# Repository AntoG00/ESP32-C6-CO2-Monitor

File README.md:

# ESP32-C6 E-Paper Air Quality Monitor

A high-precision, open-hardware environmental monitor designed to track CO2, Temperature, and Humidity levels. The device is built around the RISC-V based ESP32-C6 and features a raw E-Paper panel with a custom-designed boost driver to ensure zero light pollution and minimal thermal self-heating.

## Key Features
*   **MCU:** Espressif **ESP32-C6-Mini-1** (RISC-V, Wi-Fi 6, BLE 5, Zigbee).
*   **Sensors:**
    *   **SCD43 (Sensirion):** Photoacoustic NDIR CO2 sensor for high-accuracy indoor air quality monitoring.
    *   **SHT45-AD1F (Sensirion):** Ultra-high precision (±1.0% RH, ±0.1°C) temperature and humidity sensor with integrated PTFE membrane for protection.
*   **Display:** **Pervasive Displays E2266QS0F1** (2.66" E-Paper/E-Ink).
*   **Power:** USB-C powered via a high-efficiency, low-noise LDO (**TLV75733**). Designed for continuous operation without batteries.

## Engineering Design Decisions
This project involved several specific hardware design challenges:

1.  **Thermal Isolation (Mechanical/Electrical):** To prevent the heat generated by the MCU and voltage regulators from biasing the sensitive SHT45 and SCD43 readings, the sensors are physically isolated on the PCB using milling slots (thermal cutouts) and thin connecting bridges.
2.  **Custom E-Paper Driver:** Instead of using a pre-made display module, I integrated the high-voltage boost converter (generating ~15V) directly onto the main PCB using a specialized power inductor ($I_{sat} > 800mA$), N-Channel MOSFET, and Schottky diode topology.
3.  **Signal Integrity:** The schematic includes specific filtering for the photoacoustic sensor's peak current demands and a dedicated boot-strapping circuit to ensure reliable flashing via the native USB interface.

## PCB Layout & Thermal Engineering
The design utilizes a **4-layer stack-up** to ensure solid Ground return paths and stable power delivery for the ESP32's RF radio.

A dedicated **thermal isolation slot** separates the board into two distinct thermal zones:
*   **Right Side (Hot Zone):** Contains the ESP32 MCU, Power Regulation, and Boost Converter.
*   **Left Side (Cold Zone):** Contains the environmental sensors, connected only by narrow FR4 bridges to minimize thermal conductivity.

## Status
*   [x] Schematic Design & Verification
*   [x] PCB Layout (4-Layer)
*   [ ] Manufacturing & Assembly

## License
MIT License

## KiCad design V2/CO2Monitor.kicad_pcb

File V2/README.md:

# Hardware V2 – ESP32‑C6 + SEN66 + 4.2" E‑Ink

This is the second hardware revision of the project. V2 replaces the SCD43 + SHT45 combo with a single Sensirion **SEN66** environmental sensor and upgrades the display.

## Main Components

- **MCU:** Espressif **ESP32‑C6 Mini**
  - Wi‑Fi 6 + BLE / 802.15.4 capable (WiFi 6, Zigbee, Thread)
- **Sensor:** Sensirion **SEN66**
  - PM1, PM2.5, PM4, PM10
  - Temperature, Relative Humidity
  - VOC Index, NOx Index, CO₂
- **Display:** Pervasive Displays **4.2" Spectra E2417QS0A3**
  - 3‑color E‑Ink
- **Status LED:** Inolux **IN‑PI33TBTPRPGPB** multi‑color LED
  - Used for debug / status indication via color patterns

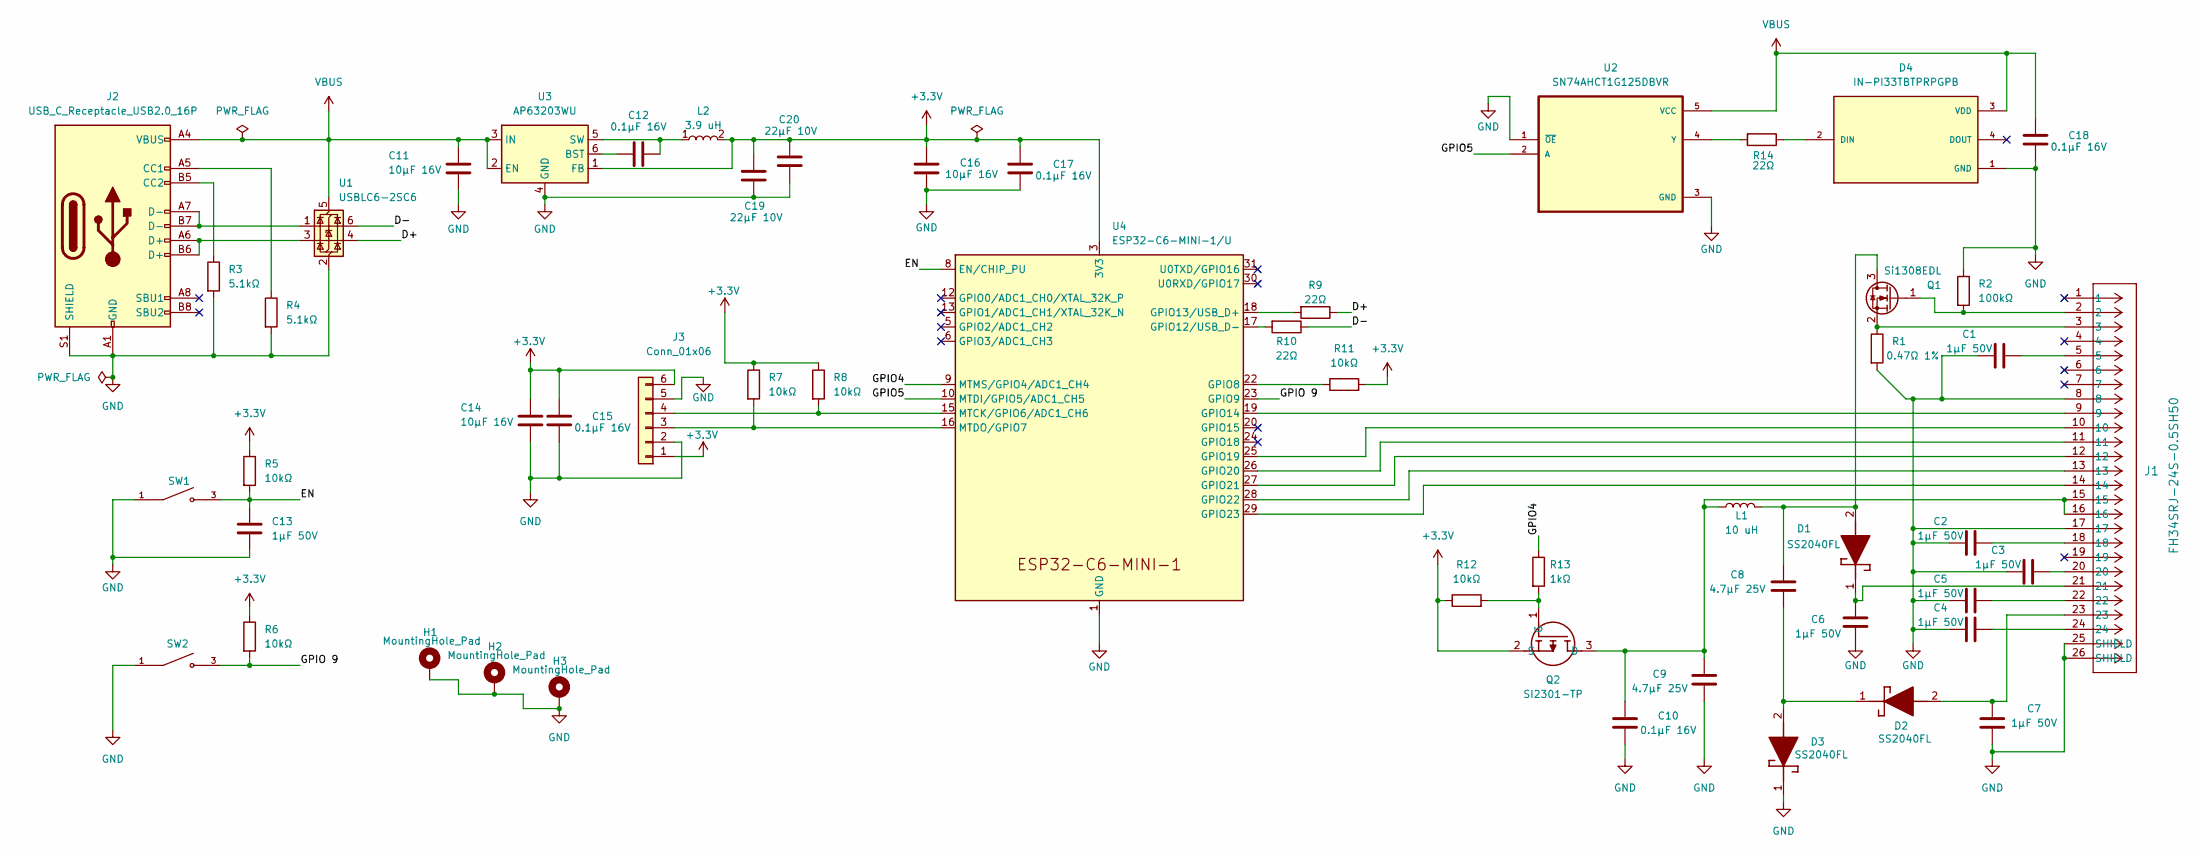
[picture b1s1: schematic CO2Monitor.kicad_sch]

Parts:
C1, C2, C3, C4, C5, C6, C7, C13: 1µF 50V; C_0603_1608Metric
C8, C9: 4.7µF 25V; C_1206_3216Metric
C10, C12, C15, C17, C18: 0.1µF 16V; C_0402_1005Metric
C11, C14, C16: 10µF 16V; C_0805_2012Metric
C19, C20: 22µF 10V; C_1206_3216Metric
D1, D2, D3: SS2040FL; SODFL3618X110N; Mouser Part Number 241-SS2040FLR100001
D4: IN-PI33TBTPRPGPB; LED_IN-PI33TBTPRPGPB; PARTREV 1.2
H1, H2, H3: MountingHole_Pad; MountingHole_3.2mm_M3_ISO14580_Pad
J1: FH34SRJ-24S-0.5SH50; CONN24x1_FH34SRJ-24S-0.5SH50_HIR
J2: USB_C_Receptacle_USB2.0_16P; GCT_USB4145-03-0230-C_REVA2
J3: Conn_01x06; JST_GH_SM06B-GHS-TB_1x06-1MP_P1.25mm_Horizontal
L1: 10 uH; L_Bourns-SRN4018
L2: 3.9 uH; INDPM5050X400N
Q1: Si1308EDL; SOT-323_SC-70
Q2: SI2301-TP; SOT95P237X125-3N; Mouser Part Number 833-SI2301-TP
R1: 0.47Ω 1%; R_1206_3216Metric
R2: 100kΩ; R_0603_1608Metric
R3, R4: 5.1kΩ; R_0603_1608Metric
R5, R6, R7, R8, R11, R12: 10kΩ; R_0603_1608Metric
R9, R10, R14: 22Ω; R_0603_1608Metric
R13: 1kΩ; R_0603_1608Metric
SW1, SW2: 2-1437565-8; SW_2-1437565-8; PARTREV V
U1: USBLC6-2SC6; SOT-23-6
U2: SN74AHCT1G125DBVR; SOT95P280X145-5N
U3: AP63203WU; TSOT-23-6
U4: ESP32-C6-MINI-1/U; ESP32-C6-MINI-1

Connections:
+3.3V: C14.1, C15.1, C16.2, C17.1, C19.1, C20.1, J3.1, J3.6, L2.2, Q2.2 (S), R5.1, R6.1, R7.1, R8.1, R11.2, R12.1, U3.1 (FB), U4.3 (3V3)
/D+: R9.1, U1.4 (I/O2)
/D-: R10.1, U1.6 (I/O1)
/EN: C13.2, R5.2, SW1.3, SW1.4, U4.8 (EN/CHIP_PU)
/GPIO4: R13.1, U4.9 (MTMS/GPIO4/ADC1_CH4)
/GPIO5: U2.2 (A), U4.10 (MTDI/GPIO5/ADC1_CH5)
/GPIO 9: R6.2, SW2.3, SW2.4, U4.23 (GPIO9)
GND: C1.1, C2.1, C3.1, C4.1, C5.1, C6.1, C7.1, C9.2, C10.2, C11.2, C13.1, C14.2, C15.2, C16.1, C17.2, C18.2, C19.2, C20.2, D3.1 (K), D4.1 (GND), H1.1, H2.1, H3.1, J1.8, J1.17, J1.25 (SHIELD), J1.26 (SHIELD), J2.A1 (GND), J2.A12 (GND), J2.B1 (GND), J2.B12 (GND), J2.S1 (SHIELD), J3.2, J3.5, R1.2, R2.1, R3.2, R4.2, SW1.1, SW1.2, SW2.1, SW2.2, U1.2 (GND), U2.1 (~OE), U2.3 (GND), U3.4 (GND), U4.1 (GND), U4.2 (GND), U4.11 (GND), U4.14 (GND), U4.36 (GND), U4.37 (GND), U4.38 (GND), U4.39 (GND), U4.40 (GND), U4.41 (GND), U4.42 (GND), U4.43 (GND), U4.44 (GND), U4.45 (GND), U4.46 (GND), U4.47 (GND), U4.48 (GND), U4.49 (GND), U4.50 (GND), U4.51 (GND), U4.52 (GND), U4.53 (GND)
unnamed: C1.2, J1.5
unnamed: C2.2, J1.18
unnamed: C3.2, J1.20
unnamed: C4.2, J1.24
unnamed: C5.2, J1.22
unnamed: C8.2, D1.2 (A), L1.2, Q1.3 (D)
unnamed: C6.2, D1.1 (K), J1.21
unnamed: C7.2, D2.2 (A), J1.23
unnamed: C8.1, D2.1 (K), D3.2 (A)
unnamed: D4.2 (DIN), R14.1
unnamed: J2.A5 (CC1), R4.1
unnamed: J2.B5 (CC2), R3.1
unnamed: J2.A6 (D+), J2.B6 (D+), U1.3 (I/O2)
unnamed: J2.A7 (D-), J2.B7 (D-), U1.1 (I/O1)
unnamed: J3.3, R7.2, U4.16 (MTDO/GPIO7)
unnamed: J3.4, R8.2, U4.15 (MTCK/GPIO6/ADC1_CH6)
unnamed: J1.2, Q1.1 (G), R2.2
unnamed: J1.3, Q1.2 (S), R1.1
unnamed: C9.1, C10.1, J1.15, J1.16, L1.1, Q2.3 (D)
unnamed: Q2.1 (G), R12.2, R13.2
unnamed: R14.2, U2.4 (Y)
unnamed: C12.1, U3.6 (BST)
unnamed: C12.2, L2.1, U3.5 (SW)
unnamed: R11.1, U4.22 (GPIO8)
unnamed: R10.2, U4.17 (GPIO12/USB_D-)
unnamed: R9.2, U4.18 (GPIO13/USB_D+)
unnamed: J1.9, U4.19 (GPIO14)
unnamed: J1.10, U4.25 (GPIO19)
unnamed: J1.11, U4.26 (GPIO20)
unnamed: J1.12, U4.27 (GPIO21)
unnamed: J1.13, U4.28 (GPIO22)
unnamed: J1.14, U4.29 (GPIO23)
VBUS: C11.1, C18.1, D4.3 (VDD), J2.A4 (VBUS), J2.A9 (VBUS), J2.B4 (VBUS), J2.B9 (VBUS), U1.5 (VBUS), U2.5 (VCC), U3.2 (EN), U3.3 (IN)

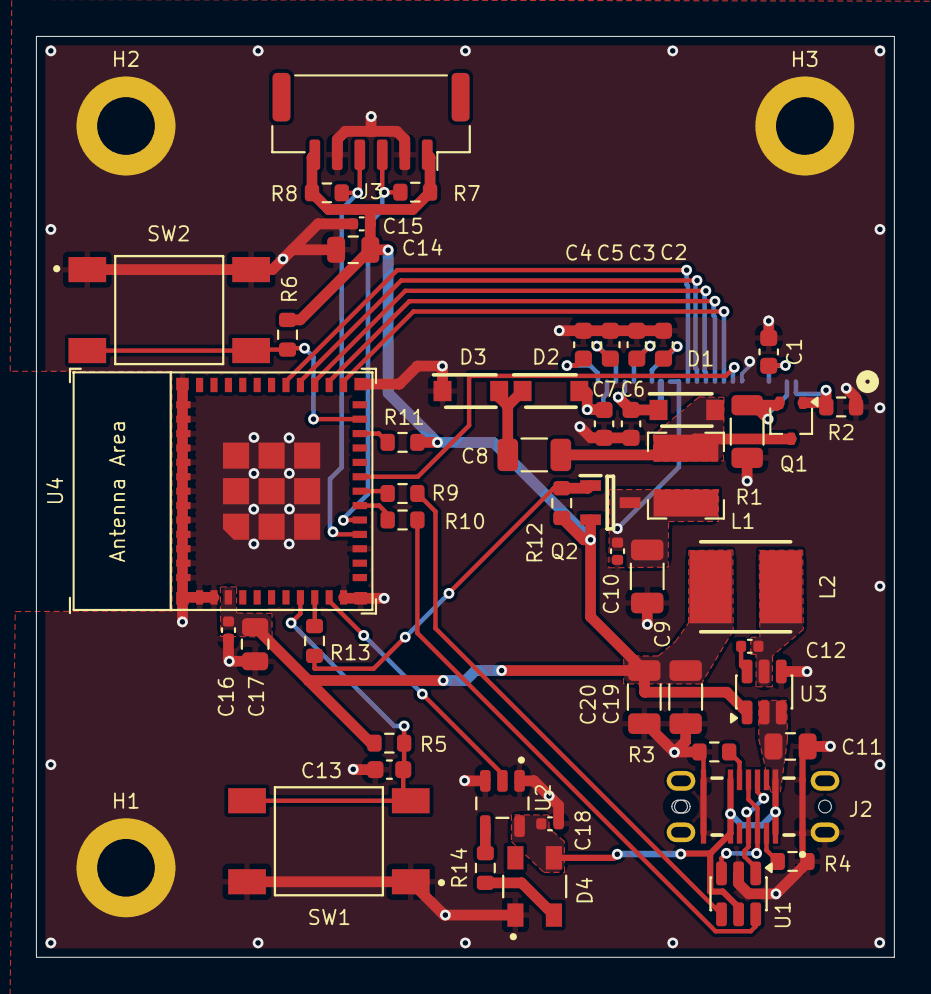
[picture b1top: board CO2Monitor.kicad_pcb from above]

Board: 2 copper layers, 47.7 x 51.2 mm, 54 parts (1 on the bottom side), 41 nets.

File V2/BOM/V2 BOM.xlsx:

|  |  | BOM
Item # | *Designator | *Qty | Manufacturer | *Mfg Part # | Description / Value | *Package/Footprint | Your Instructions / Notes
1.0 | C1,C2,C3,C4,C5,C6,C7,C13 | 8.0 |  | 1µF 50V | Cap Ceramic 1µF 50V X7R 10% | Capacitor_SMD:C_0603_1608Metric
2.0 | C8,C9 | 2.0 |  | 4.7µF 25V | Cap Ceramic 4.7µF 25V X7R 10% | Capacitor_SMD:C_1206_3216Metric
3.0 | C10,C12,C15,C17,C18 | 5.0 |  | 0.1µF 16V | Cap Ceramic 0.1µF 16V (or 25V) X7R 10% | Capacitor_SMD:C_0402_1005Metric
4.0 | C11,C14,C16 | 3.0 |  | 10µF 16V | Cap Ceramic 10µF 16V (or 25V) X5R/X7R 10% | Capacitor_SMD:C_0805_2012Metric
5.0 | C19,C20 | 2.0 |  | 22µF 10V | Cap Ceramic 22µF 10V (or 16V) X5R/X7R 20% | Capacitor_SMD:C_1206_3216Metric
6.0 | D1,D2,D3 | 3.0 | Panjit | SS2040FL_R1_00001 | Schottky Diodes & Rectifiers 40V,Schottky,SOD-123FL,2A | SS2040FL:SODFL3618X110N | https://www2.mouser.com/datasheet/3/3736/1/774A80C0874A6CB80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
7.0 | D4 | 1.0 | Inolux | IN-PI33TBTPRPGPB | Multi-Colour LEDs Top View / PLCC / 3.5 x 3.5 x 1.95 / 4-pin / Tricolor with IC | IN-PI33TBTPRPGPB:LED_IN-PI33TBTPRPGPB | https://www2.mouser.com/datasheet/3/760/1/IN_PI33TBTPRPGPB_v1.2.pdf
8.0 | J1 | 1.0 | Hirose Connector | FH34SRJ-24S-0.5SH50 | FFC & FPC Connectors 24POS .5MM | FH34SRJ-24S-0.5SH(50):CONN24x1_FH34SRJ-24S-0.5SH50_HIR | https://www2.mouser.com/datasheet/3/731/1/FH34SRJ_24S_0.5SH_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
9.0 | J2 | 1.0 | GCT | USB4145-03-0230-C | USB Connectors USB-C Rec 3u" Vert 16P SMT 2.3mm TH stakes H7.46mm T+R+Cap | USB4145-03-0230-C:GCT_USB4145-03-0230-C_REVA2 | https://www.mouser.com/catalog/specsheets/Global_Connector_T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
10.0 | J3 | 1.0 | JST Commercial | SM06B-GHS-TB | Headers & Wire Housings | Connector_JST:JST_GH_SM06B-GHS-TB_1x06-1MP_P1.25mm_Horizontal | https://www2.mouser.com/datasheet/3/1070/1/eGH.pdf
11.0 | L1 | 1.0 | Bourns | SRN4018-100M | Power Inductors - SMD 10uH 20% SMD 4018 | Inductor_SMD:L_Bourns-SRN4018 | Power Inductor, Shielded, Isat > 0.5A, DCR < 0.5Ω
12.0 | L2 | 1.0 | Bourns | SRN5040-4R7M | Power Inductors - SMD 4.7uH 20% SMD 5040 | SRN5040:INDPM5050X400N | 4.7 µH SMD shielded/semi‑shielded power inductor, Irms ≥ 3.0 A, Isat ≥ 3.0 A, D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
13.0 | Q1 | 1.0 | Vishay | SI1308EDL-T1-GE3 | MOSFETs 30V Vds 12V Vgs SC70-3 | Package_TO_SOT_SMD:SOT-323_SC-70 | https://www.vishay.com/doc?63399
14.0 | Q2 | 1.0 | Micro Commercial Components (MCC) | SI2301-TP | MOSFETs P-CH -20V -2.8A 8S | SI2301-TP:SOT95P237X125-3N | https://eu.mouser.com/datasheet/3/225/1/SI2301(SOT-23).pdf
15.0 | R1 | 1.0 |  | 0.47Ω 1% | Res Current Sense 0.47Ω 1% 1/4W | Resistor_SMD:R_1206_3216Metric
16.0 | R2 | 1.0 |  | 100kΩ | Res Thick Film 100kΩ 1% 1/10W | Resistor_SMD:R_0603_1608Metric
17.0 | R3,R4 | 2.0 |  | 5.1kΩ | Res Thick Film 5.1kΩ 1% 1/10W | Resistor_SMD:R_0603_1608Metric
18.0 | R5,R6,R7,R8,R11,R12 | 6.0 |  | 10kΩ | Res Thick Film 10kΩ 1% 1/10W | Resistor_SMD:R_0603_1608Metric
19.0 | R9,R10,R14 | 3.0 |  | 22Ω | Res Thick Film 22Ω 1% 1/10W | Resistor_SMD:R_0603_1608Metric
20.0 | R13 | 1.0 |  | 1kΩ | Res Thick Film 1kΩ 1% 1/10W | Resistor_SMD:R_0603_1608Metric
21.0 | SW1,SW2 | 2.0 | TE Connectivity / P&B | 2-1437565-8 | Tactile Switches TACTILE 260G FORCE S | TE Connectivity 2-1437565-8:SW_2-1437565-8 | Or Generic 6x6mm SMD Switch
22.0 | U1 | 1.0 | STMicroelectronics | USBLC6-2SC6 | ESD Protection Diodes / TVS Diodes ESD Protection Low Cap | Package_TO_SOT_SMD:SOT-23-6 | https://www.st.com/resource/en/datasheet/usblc6-2.pdf
23.0 | U2 | 1.0 | Texas Instruments | SN74AHCT1G125DBVR | Buffers & Line Drivers Tri-State Single Bus A 595-SN74AHCT1G125 A 595-SN74AHCT1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 | SN74AHCT1G125DBVR:SOT95P280X145-5N | https://www.ti.com/lit/gpn/sn74ahct1g125
24.0 | U3 | 1.0 | Diodes Incorporated | AP63203WU | Switching Voltage Regulators DCDC Conv HV Buck TSOT26 T&R 3K | Package_TO_SOT_SMD:TSOT-23-6 | https://4donline.ihs.com/images/VipMasterIC/IC/DIOD/DIOD-S-A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
25.0 | U4 | 1.0 | Espressif Systems | ESP32-C6-MINI-1-H8 | ESP32-C6-MINI-1-H8 | PCM_Espressif:ESP32-C6-MINI-1 | https://www.mouser.com/catalog/specsheets/Espressif_Systems_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
Need a quick and accurante quote? Need an efficient production? Please read SMT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
Click for Instructions on How to Create a BOM

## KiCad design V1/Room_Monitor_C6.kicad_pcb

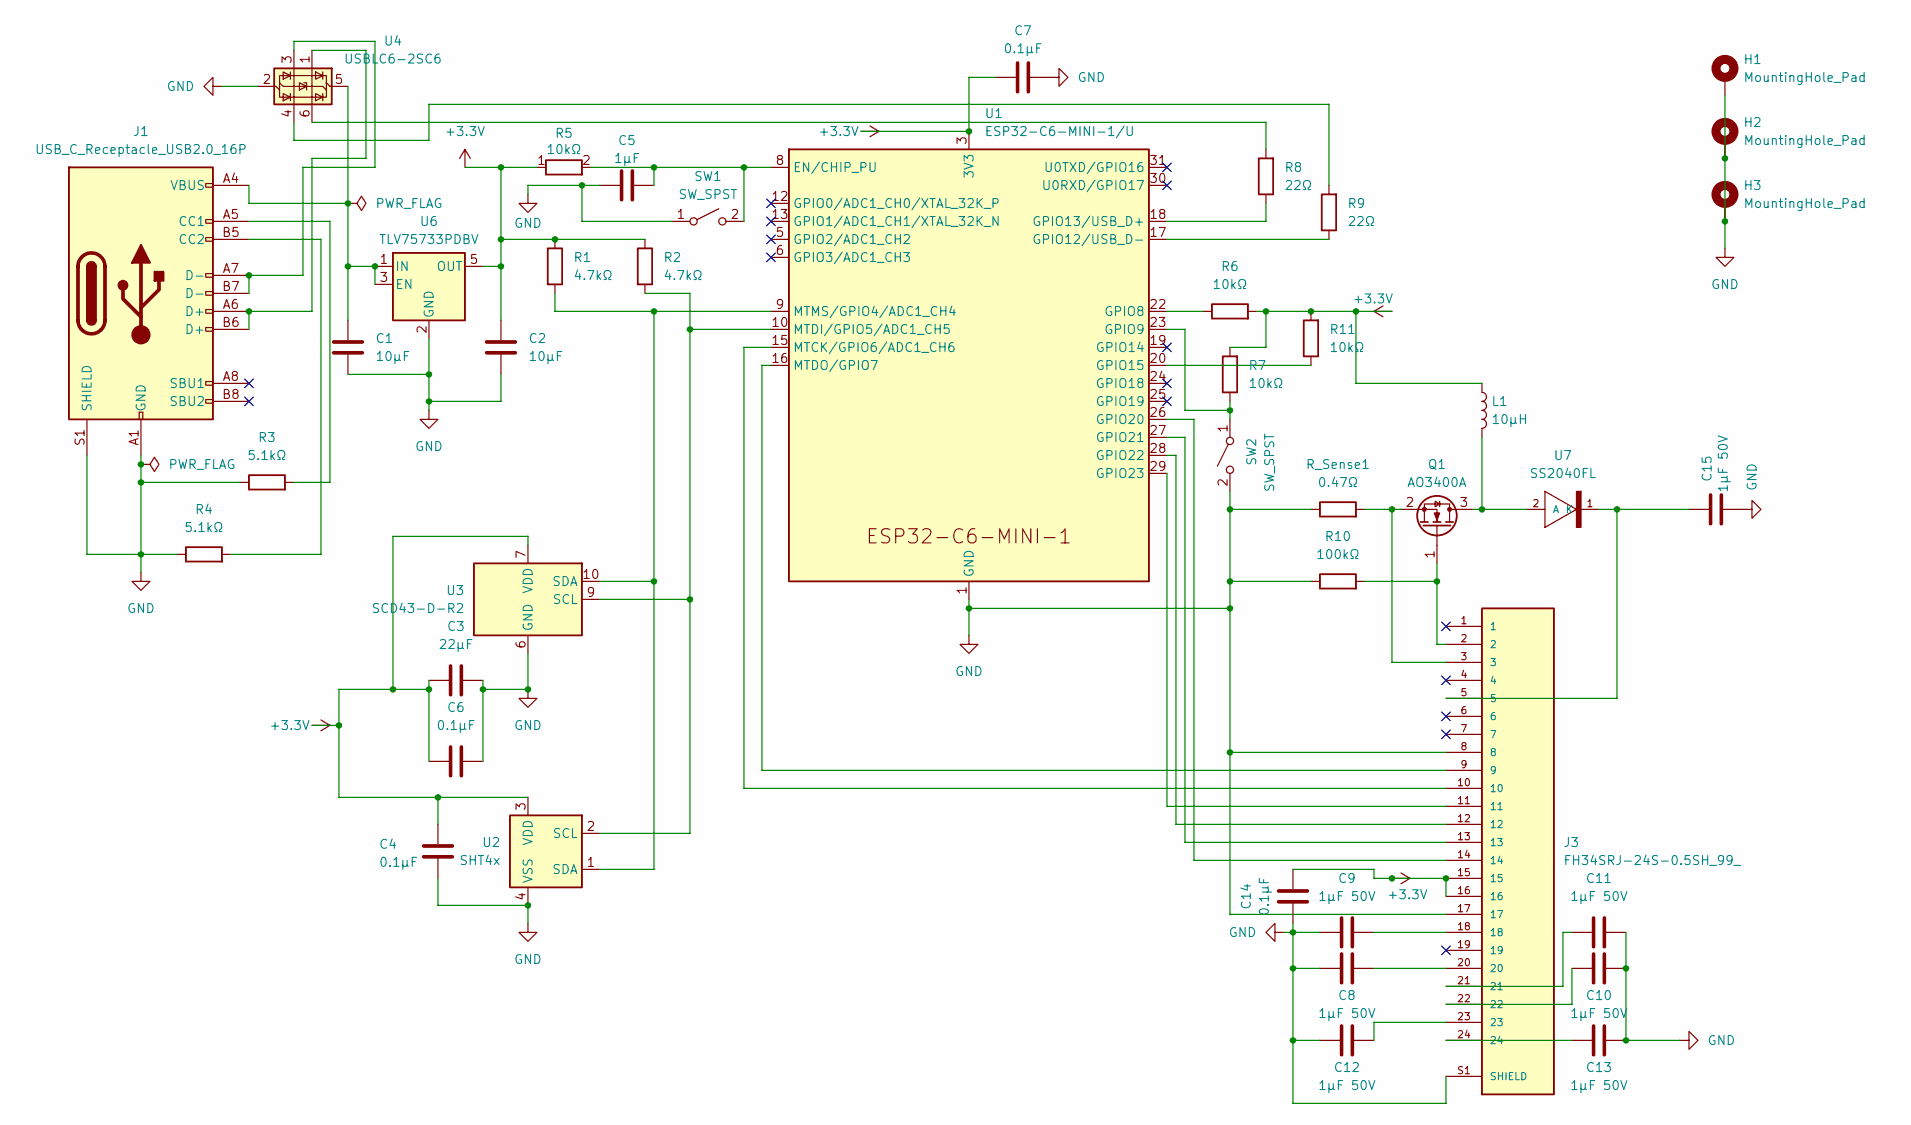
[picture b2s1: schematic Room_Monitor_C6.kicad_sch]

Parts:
C1, C2: 10µF; C_0805_2012Metric
C3: 22µF; C_0805_2012Metric
C4, C6, C7, C14: 0.1µF; C_0402_1005Metric
C5: 1µF; C_0402_1005Metric
C8, C9, C10, C11, C12, C13, C15: 1µF 50V; C_0603_1608Metric
H1, H2, H3: MountingHole_Pad; MountingHole_2.2mm_M2_Pad
J1: USB_C_Receptacle_USB2.0_16P; USB_C_Receptacle_GCT_USB4105-xx-A_16P_TopMnt_Horizontal
J3: FH34SRJ-24S-0.5SH_99_; HRS_FH34SRJ-24S-0.5SH_99_; PARTREV NA; DigiKey_Part_Number H124725CT-ND
L1: 10µH; L_Taiyo-Yuden_NR-40xx
Q1: AO3400A; SOT-23
R1, R2: 4.7kΩ; R_0603_1608Metric
R3, R4: 5.1kΩ; R_0603_1608Metric
R5, R6, R7, R11: 10kΩ; R_0603_1608Metric
R8, R9: 22Ω; R_0603_1608Metric
R10: 100kΩ; R_0603_1608Metric
R_Sense1: 0.47Ω; R_1206_3216Metric
SW1, SW2: SW_SPST; SW_SPST_SKQG_WithoutStem
U1: ESP32-C6-MINI-1/U; ESP32-C6-MINI-1
U2: SHT4x; Sensirion_DFN-4_1.5x1.5mm_P0.8mm_SHT4x_NoCentralPad
U3: SCD43-D-R2; Sensirion_SCD4x-1EP_10.1x10.1mm_P1.25mm_EP4.8x4.8mm
U4: USBLC6-2SC6; SOT-23-6
U6: TLV75733PDBV; SOT-23-5
U7: SS2040FL; D_SOD-123F

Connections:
+3.3V: C2.1, C3.1, C4.2, C6.1, C7.1, C14.2, J3.15, J3.16, L1.1, R1.1, R2.1, R5.1, R6.2, R7.2, R11.2, U1.3 (3V3), U2.3 (VDD), U3.7 (VDD), U3.19 (VDD), U6.5 (OUT)
GND: C1.2, C2.2, C3.2, C4.1, C5.1, C6.2, C7.2, C8.2, C9.1, C10.1, C11.2, C12.2, C13.1, C14.1, C15.1, H1.1, H2.1, H3.1, J1.A1 (GND), J1.A12 (GND), J1.B1 (GND), J1.B12 (GND), J1.S1 (SHIELD), J3.8, J3.17, J3.S1 (SHIELD), J3.S2 (SHIELD), R3.1, R4.1, R10.1, R_Sense1.1, SW1.1 (A), SW2.2 (B), U1.1 (GND), U1.2 (GND), U1.11 (GND), U1.14 (GND), U1.36 (GND), U1.37 (GND), U1.38 (GND), U1.39 (GND), U1.40 (GND), U1.41 (GND), U1.42 (GND), U1.43 (GND), U1.44 (GND), U1.45 (GND), U1.46 (GND), U1.47 (GND), U1.48 (GND), U1.49 (GND), U1.50 (GND), U1.51 (GND), U1.52 (GND), U1.53 (GND), U2.4 (VSS), U3.6 (GND), U3.20 (GND), U3.21 (GND), U4.2 (GND), U6.2 (GND)
unnamed: C8.1, J3.20
unnamed: C9.2, J3.18
unnamed: C10.2, J3.22
unnamed: C11.1, J3.21
unnamed: C12.1, J3.23
unnamed: C13.2, J3.24
unnamed: J1.A5 (CC1), R3.2
unnamed: J1.B5 (CC2), R4.2
unnamed: J1.A6 (D+), J1.B6 (D+), U4.1 (I/O1)
unnamed: J1.A7 (D-), J1.B7 (D-), U4.3 (I/O2)
unnamed: L1.2, Q1.3 (D), U7.2 (A)
unnamed: J3.2, Q1.1 (G), R10.2
unnamed: J3.3, Q1.2 (S), R_Sense1.2
unnamed: R8.2, U4.6 (I/O1)
unnamed: R9.2, U4.4 (I/O2)
unnamed: C5.2, R5.2, SW1.2 (B), U1.8 (EN/CHIP_PU)
unnamed: R7.1, SW2.1 (A), U1.23 (GPIO9)
unnamed: R6.1, U1.22 (GPIO8)
unnamed: R9.1, U1.17 (GPIO12/USB_D-)
unnamed: R8.1, U1.18 (GPIO13/USB_D+)
unnamed: R11.1, U1.20 (GPIO15)
unnamed: J3.14, U1.26 (GPIO20)
unnamed: J3.13, U1.27 (GPIO21)
unnamed: J3.12, U1.28 (GPIO22)
unnamed: J3.11, U1.29 (GPIO23)
unnamed: J3.10, U1.15 (MTCK/GPIO6/ADC1_CH6)
unnamed: R2.2, U1.10 (MTDI/GPIO5/ADC1_CH5), U2.2 (SCL), U3.9 (SCL)
unnamed: J3.9, U1.16 (MTDO/GPIO7)
unnamed: R1.2, U1.9 (MTMS/GPIO4/ADC1_CH4), U2.1 (SDA), U3.10 (SDA)
unnamed: C1.1, J1.A4 (VBUS), J1.A9 (VBUS), J1.B4 (VBUS), J1.B9 (VBUS), U4.5 (VBUS), U6.1 (IN), U6.3 (EN)
unnamed: C15.2, J3.5, U7.1 (K)

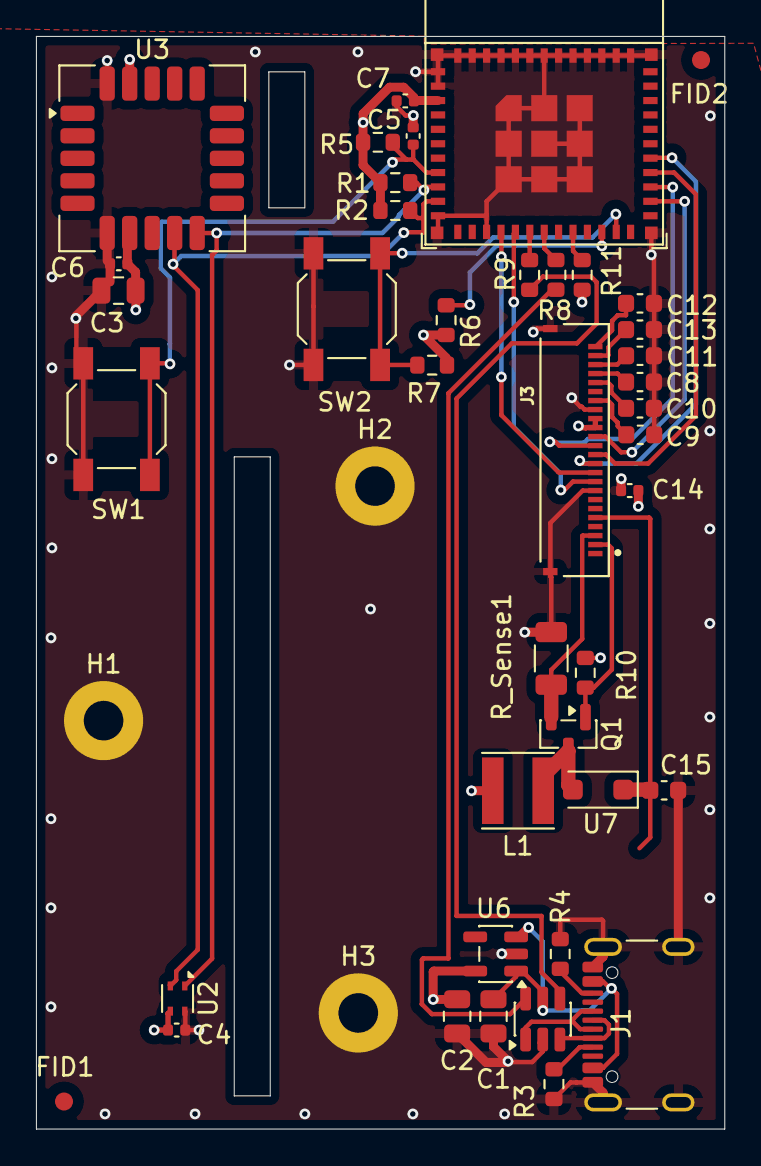
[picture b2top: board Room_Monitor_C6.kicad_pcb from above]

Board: 4 copper layers, 38.2 x 60.7 mm, 44 parts (0 on the bottom side), 33 nets.

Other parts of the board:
FID1, FID2: Fiducial; Fiducial_1mm_Mask2mm

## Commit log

2025-11-29 Initial Schematic Release
2025-12-01 Completed 4-layer PCB layout
2025-12-01 White background Room_Monitor_C6.svg
2025-12-10 Added v2 folder/readme for new SEN66 + ESP32C6 board
2025-12-10 Add v1 folder for original board
2025-12-10 Move V1 files in correct folder
